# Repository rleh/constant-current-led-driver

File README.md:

# Constant Current LED Driver

*WORK IN PROGRESS!*

Goal of this project is to design a constant current LED driver for high power LED modules.
To be able to use large LED modules (e.g. V_FW = 35V) or multiple modules in series boost topology is used.
The maximum output voltage is configurable up to 70V to allow two 35V modules in series.

TIs [LM3424](http://www.ti.com/lit/ds/symlink/lm3424.pdf) chip is used in this design.

The current is adjustable, 827mA for the LED module [*Nichia NFCLJ108B-V1*](www.fairchip.com/pdf/Nichia/NFCLJ108B-V1.pdf)
and 389mA for [*Nichia NFCLL060B-V1*](https://lumstatic.com/Ke/DG/JkgO4GaB6Fu6ut0LEA.pdf) are testet.

To adjust the LED brightness a PWM input is available, that can be used for strobe light too.
Additionally multiple driver modules can be syncronized using the SYNC input.

In order to protect the LED from thermal destruction, the current is reduced from a temperature of 70°C until it is switched off at approx. 90°C (thermal foldback).
For this purpose an NTC (Vishay NTCLE100E3104JB0) can be attached to the LED.
If this feature is not required, a 100kΩ must be soldered in instead of the NTC.

Any 18V..20V (cheap) notebook power supply with a sufficient power rating can be used as an AC adapter.

## LED Driver PCB

### Specs
* Input: 12V to 24V
* Output: Up to 20 LEDs (70V) at 827mA or 389mA
* 70°C - 90°C Thermal Foldback
* 1.5MHz Switching Frequency
* PWM Dimming up to 30 kHz (?)

### Parts

| Designator | Part                   | MPN                | Quantity | Prize@1 | Prize@10 |
| ---------- | ---------------------- | ------------------ | -------- | ------- | -------- |
| U1         | LM3424                 | LM3424MHX          | 1        | 2.73$   | 2.45$    |
| Q2,Q3      | PSMN025-80YLX          | PSMN025-80YLX      | 2        | 0.57$   | 0.51$    |
| L1         | WE-PD 7447709220       | 7447709220         | 1        | 2.41$   | 2.20$    |
| L1         | **or** MSS1210-153ME   | MSS1210-153ME      | 1        | 2.19€   | 1.96€    |
| D1         | VSSAF5M10-M3/H         | VSSAF5M10-M3/H     | 1        | 0.45$   | 0.36$    |
| D1         | **or** SL510AFL-TP     | SL510AFL-TP        | 1        | 0.54$   | 0.46$    |
| Q1         | 2N7002                 | T2N7002AK,LM       | 1        | 0.15$   | 0.13$    |
| NTC        | NTCLE100E3104JB0       | NTCLE100E3104JB0   | 1        | 0.69$   | 0.57$    |
| C4         | EEH-ZC1K470P           | EEH-ZC1K470P       | 1        | 2.14$   | 1.72$    |
| C1,C12,C13 | 4.7µF, 100V, X7R, 1210 | C1210X475K101T     | 3        | 0.41$   | 0.30$    |
| C2,C3,C14  | 10µF, 100V, X7R, 2220  | FS55X106K101EHG    | 3        | 0.47$   | 0.35$    |
| R15        | 100mΩ, 0805, 1W        | RUT2012FR100CS     | 1        | 0.30$   | 0.26$    |
| R13        | 60mΩ, 0805, 1W         | RLP73M2AR062FTDF   | 1        | 0.52$   | 0.45$    |
| other R    | 8 distinct values      | MPN                | 17       | 0.05$   | 0.01$    |
| other C    | 5 distinct values      | MPN                | 10       | 0.10$   | 0.02$    |

**Total Cost**: approx. 14$ @ 1pcs; <12$ @ 10pcs

## License

Copyright Raphael Lehmann 2019

Licensed under CERN OHL Version 1.2

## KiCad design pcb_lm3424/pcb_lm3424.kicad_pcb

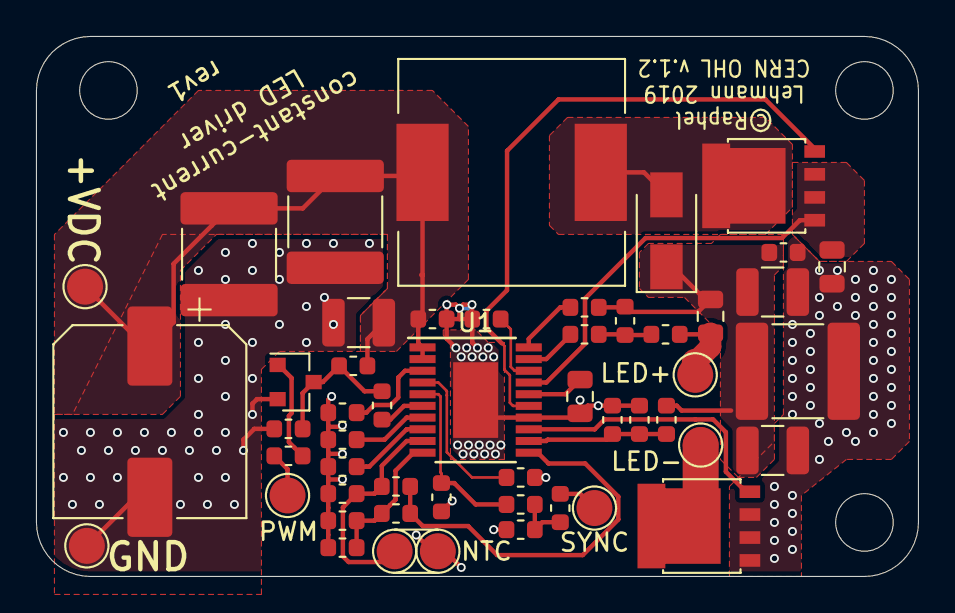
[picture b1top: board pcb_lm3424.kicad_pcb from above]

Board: 2 copper layers, 49.0 x 30.0 mm, 54 parts (0 on the bottom side), 29 nets.

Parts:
C1: CIN; C_1210_3225Metric
C2, C3: CIN; C_2220_5650Metric
C4: CIN; CP_Elec_10x10.5
C5, C8, C11, C16: 100n; C_0603_1608Metric
C6, C7: 270n; C_0603_1608Metric
C9: 2µ2 X7R 16V 0805; C_0805_2012Metric
C10: DNP; C_0603_1608Metric
C12, C13: COUT; C_1210_3225Metric
C14: COUT; C_2220_5650Metric
C15: 47p; C_0603_1608Metric
C17, C18: 100p; C_0603_1608Metric
D1: VSSAF5M10-M3/H (DO-221AC); D_SMA
H1, H2, H3: M3; MountingHole_3.2mm_M3
J1: PWM; TestPoint_Pad_D2.0mm
J2: VIN; TestPoint_Pad_D2.0mm
J3: SYNC; TestPoint_Pad_D2.0mm
J4: GND; TestPoint_Pad_D2.0mm
J5, J6: NTC; TestPoint_Pad_D2.0mm
J7: +; TestPoint_Pad_D2.0mm
J8: –; TestPoint_Pad_D2.0mm
L1: MSS1210-104KE; L_12x12mm_H8mm
Q1: 2N7002; SOT-23
Q2, Q3: PSMN025-80YLX; LFPAK56
R1, R14, R19: 0; R_0603_1608Metric
R2, R11: 10k; R_0603_1608Metric
R3, R17: 1k8; R_0603_1608Metric
R4, R7, R8, R12: 15k; R_0603_1608Metric
R5, R6: 4k7; R_0603_1608Metric
R9, R10: 1k|470; R_0603_1608Metric
R13: 60m 1W; R_0805_2012Metric
R15: 100m 1W; R_0805_2012Metric
R16: 120k; R_0603_1608Metric
R18: 150; R_0603_1608Metric
U1: LM3424; ETSSOP-20-1EP_4.4x6.5mm_P0.65mm_EP3x4.2mm

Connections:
+VDC: C1.1, C2.1, C3.1, C4.1, C16.1, J2.1, L1.1, R2.1, U1.1, U1.2
/PWM: J1.1, R1.2
/VCC: C9.2, U1.16
/nDIM: Q1.3, R2.2, R3.1, R19.2
GND: C1.2, C2.2, C3.2, C4.2, C5.2, C6.2, C7.2, C8.2, C9.1, C11.2, C12.2, C13.2, C14.2, C15.2, C16.2, C17.2, J4.1, J6.1, Q1.2, Q3.1, Q3.2, Q3.3, R3.2, R4.2, R5.2, R6.2, R7.2, R11.1, R13.2, R17.2, U1.14, U1.21
unnamed: C5.1, U1.3
unnamed: C6.1, U1.7
unnamed: C7.1, R7.1, R8.2, U1.10
unnamed: C8.1, J5.1, R12.2, U1.9
unnamed: C10.1, C11.1, C12.1, C13.1, C14.1, D1.1, R9.1, R15.1, R16.1
unnamed: C10.2, R10.1, R14.2
unnamed: C15.1, R16.2, R17.1, U1.12
unnamed: C17.1, C18.1, R18.1
unnamed: C18.2, R5.1, U1.5
unnamed: D1.2, L1.2, Q2.5
unnamed: J3.1, R18.2
unnamed: J7.1, R14.1, R15.2
unnamed: J8.1, Q3.5
unnamed: Q1.1, R1.1
unnamed: Q2.1, Q2.2, Q2.3, R13.1, U1.17
unnamed: Q2.4, U1.15
unnamed: Q3.4, U1.13
unnamed: R4.1, U1.4
unnamed: R6.1, U1.8
unnamed: R9.2, U1.20
unnamed: R10.2, U1.19
unnamed: R11.2, U1.18
unnamed: R8.1, R12.1, U1.11
unnamed: R19.1, U1.6

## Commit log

2019-08-18 License added
2019-08-18 README added
2019-08-18 Lib: add LM3424 symbol
2019-08-18 Lib: add MSS1210 3d model
2019-08-18 Add PCB schematic
2019-08-18 Add PCB layout
2019-08-18 README: Specs
2019-08-19 Change inductor
2019-08-19 Add BOM
2019-08-25 Gerber settings
2019-08-26 Add panel with 4 PCBs

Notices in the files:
pcb_lm3424/pcb_lm3424.kicad_pcb:
©Raphel
CERN OHL v.1.2
